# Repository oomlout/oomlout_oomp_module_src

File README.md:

# 

* ibom github: [ibom github](kicad\current_version\working\bom\ibom.html)
* ibom direct: [ibom direct](https://raw.githack.com/oomlout//main/kicad/current_version/working/bom/ibom.html)

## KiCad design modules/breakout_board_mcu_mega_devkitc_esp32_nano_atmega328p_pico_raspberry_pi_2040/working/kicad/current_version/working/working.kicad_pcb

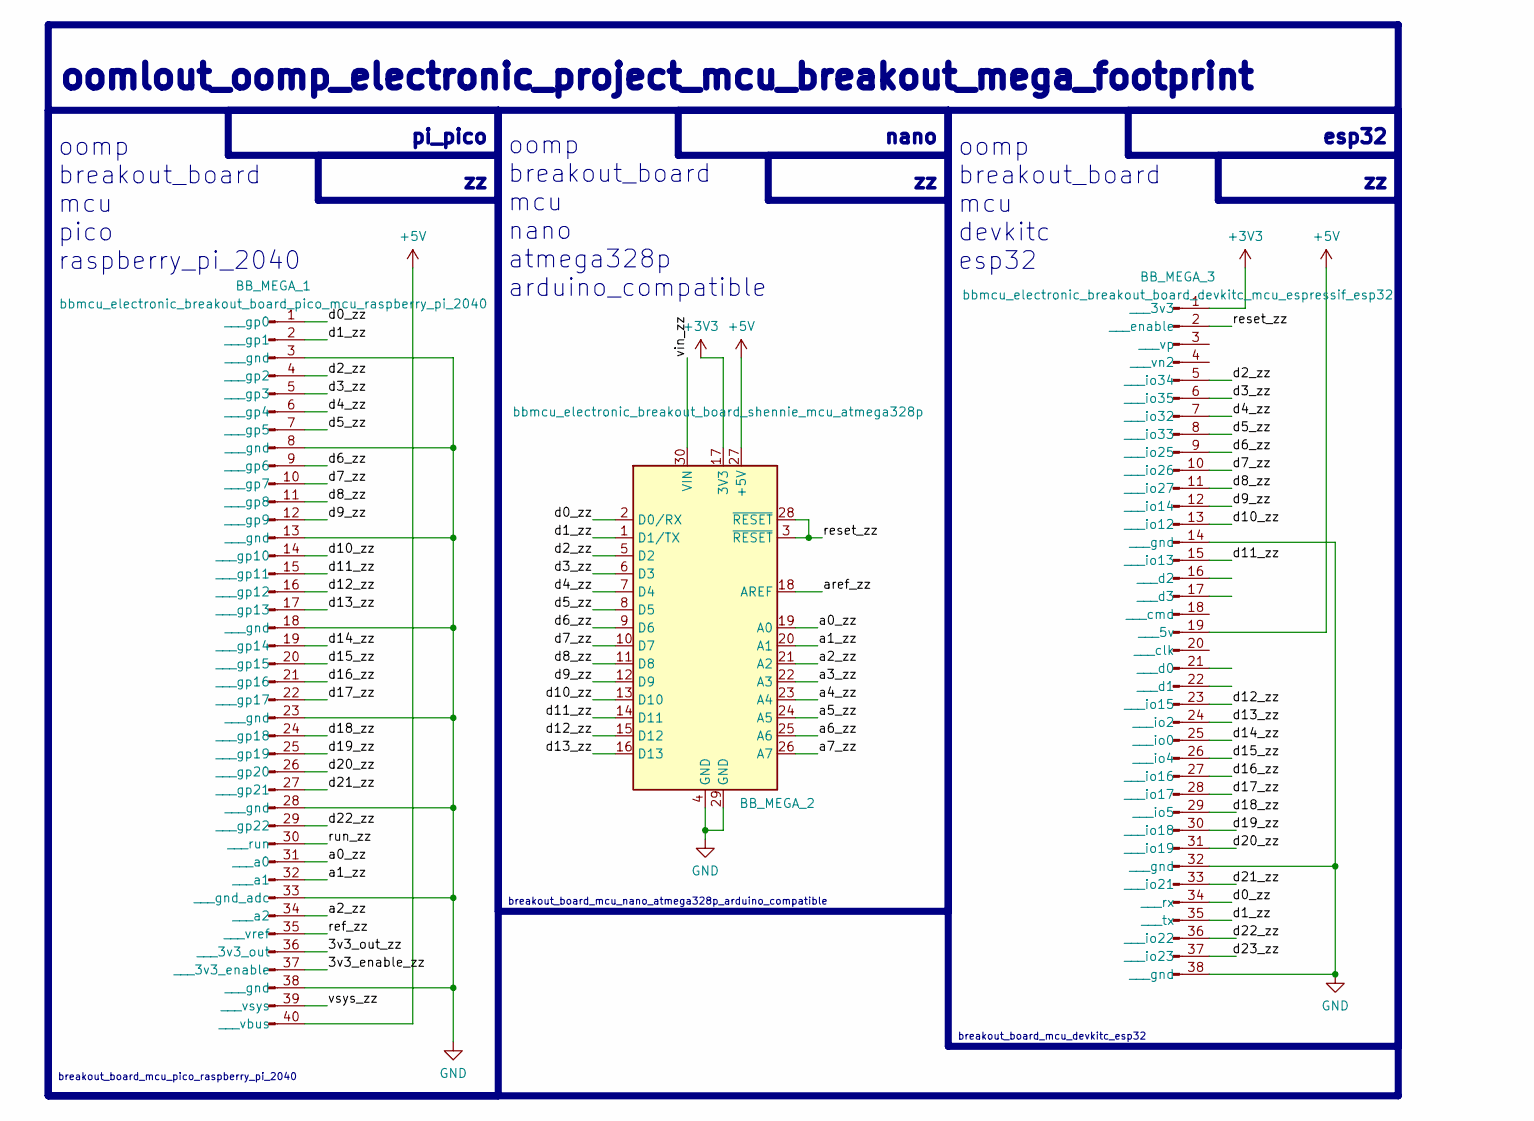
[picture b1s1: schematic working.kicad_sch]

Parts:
BB_MEGA_1: bbmcu_electronic_breakout_board_pico_mcu_raspberr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; bbmcu_electronic_breakout_board_pico_mcu_raspberry_pi_2040
BB_MEGA_2: bbmcu_electronic_breakout_board_shennie_mcu_atmeg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; bbmcu_electronic_breakout_board_shennie_mcu_atmega328p_ardu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
BB_MEGA_3: bbmcu_electronic_breakout_board_devkitc_mcu_espre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; bbmcu_electronic_breakout_board_devkitc_mcu_espressif_esp32

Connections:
+3V3: BB_MEGA_2.17 (3V3), BB_MEGA_3.1 (___3v3)
+5V: BB_MEGA_1.40 (___vbus), BB_MEGA_2.27 (+5V), BB_MEGA_3.19 (___5v)
/3v3_enable_zz: BB_MEGA_1.37 (___3v3_enable)
/3v3_out_zz: BB_MEGA_1.36 (___3v3_out)
/a0_zz: BB_MEGA_1.31 (___a0), BB_MEGA_2.19 (A0)
/a1_zz: BB_MEGA_1.32 (___a1), BB_MEGA_2.20 (A1)
/a2_zz: BB_MEGA_1.34 (___a2), BB_MEGA_2.21 (A2)
/a3_zz: BB_MEGA_2.22 (A3)
/a4_zz: BB_MEGA_2.23 (A4)
/a5_zz: BB_MEGA_2.24 (A5)
/a6_zz: BB_MEGA_2.25 (A6)
/a7_zz: BB_MEGA_2.26 (A7)
/aref_zz: BB_MEGA_2.18 (AREF)
/d0_zz: BB_MEGA_1.1 (___gp0), BB_MEGA_2.2 (D0/RX), BB_MEGA_3.34 (___rx)
/d1_zz: BB_MEGA_1.2 (___gp1), BB_MEGA_2.1 (D1/TX), BB_MEGA_3.35 (___tx)
/d2_zz: BB_MEGA_1.4 (___gp2), BB_MEGA_2.5 (D2), BB_MEGA_3.5 (___io34)
/d3_zz: BB_MEGA_1.5 (___gp3), BB_MEGA_2.6 (D3), BB_MEGA_3.6 (___io35)
/d4_zz: BB_MEGA_1.6 (___gp4), BB_MEGA_2.7 (D4), BB_MEGA_3.7 (___io32)
/d5_zz: BB_MEGA_1.7 (___gp5), BB_MEGA_2.8 (D5), BB_MEGA_3.8 (___io33)
/d6_zz: BB_MEGA_1.9 (___gp6), BB_MEGA_2.9 (D6), BB_MEGA_3.9 (___io25)
/d7_zz: BB_MEGA_1.10 (___gp7), BB_MEGA_2.10 (D7), BB_MEGA_3.10 (___io26)
/d8_zz: BB_MEGA_1.11 (___gp8), BB_MEGA_2.11 (D8), BB_MEGA_3.11 (___io27)
/d9_zz: BB_MEGA_1.12 (___gp9), BB_MEGA_2.12 (D9), BB_MEGA_3.12 (___io14)
/d10_zz: BB_MEGA_1.14 (___gp10), BB_MEGA_2.13 (D10), BB_MEGA_3.13 (___io12)
/d11_zz: BB_MEGA_1.15 (___gp11), BB_MEGA_2.14 (D11), BB_MEGA_3.15 (___io13)
/d12_zz: BB_MEGA_1.16 (___gp12), BB_MEGA_2.15 (D12), BB_MEGA_3.23 (___io15)
/d13_zz: BB_MEGA_1.17 (___gp13), BB_MEGA_2.16 (D13), BB_MEGA_3.24 (___io2)
/d14_zz: BB_MEGA_1.19 (___gp14), BB_MEGA_3.25 (___io0)
/d15_zz: BB_MEGA_1.20 (___gp15), BB_MEGA_3.26 (___io4)
/d16_zz: BB_MEGA_1.21 (___gp16), BB_MEGA_3.27 (___io16)
/d17_zz: BB_MEGA_1.22 (___gp17), BB_MEGA_3.28 (___io17)
/d18_zz: BB_MEGA_1.24 (___gp18), BB_MEGA_3.29 (___io5)
/d19_zz: BB_MEGA_1.25 (___gp19), BB_MEGA_3.30 (___io18)
/d20_zz: BB_MEGA_1.26 (___gp20), BB_MEGA_3.31 (___io19)
/d21_zz: BB_MEGA_1.27 (___gp21), BB_MEGA_3.33 (___io21)
/d22_zz: BB_MEGA_1.29 (___gp22), BB_MEGA_3.36 (___io22)
/d23_zz: BB_MEGA_3.37 (___io23)
/ref_zz: BB_MEGA_1.35 (___vref)
/reset_zz: BB_MEGA_2.3 (~RESET), BB_MEGA_2.28 (~RESET), BB_MEGA_3.2 (___enable)
/run_zz: BB_MEGA_1.30 (___run)
/vin_zz: BB_MEGA_2.30 (VIN)
/vsys_zz: BB_MEGA_1.39 (___vsys)
GND: BB_MEGA_1.3 (___gnd), BB_MEGA_1.8 (___gnd), BB_MEGA_1.13 (___gnd), BB_MEGA_1.18 (___gnd), BB_MEGA_1.23 (___gnd), BB_MEGA_1.28 (___gnd), BB_MEGA_1.33 (___gnd_adc), BB_MEGA_1.38 (___gnd), BB_MEGA_2.4 (GND), BB_MEGA_2.29 (GND), BB_MEGA_3.14 (___gnd), BB_MEGA_3.32 (___gnd), BB_MEGA_3.38 (___gnd)

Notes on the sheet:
oomlout_oomp_electronic_project_mcu_breakout_mega_footprint
oomp breakout_board mcu pico raspberry_pi_2040
nano
breakout_board_mcu_pico_raspberry_pi_2040
oomp breakout_board mcu nano atmega328p arduino_compatible
breakout_board_mcu_nano_atmega328p_arduino_compatible
pi_pico
breakout_board_mcu_devkitc_esp32
oomp breakout_board mcu devkitc esp32
esp32

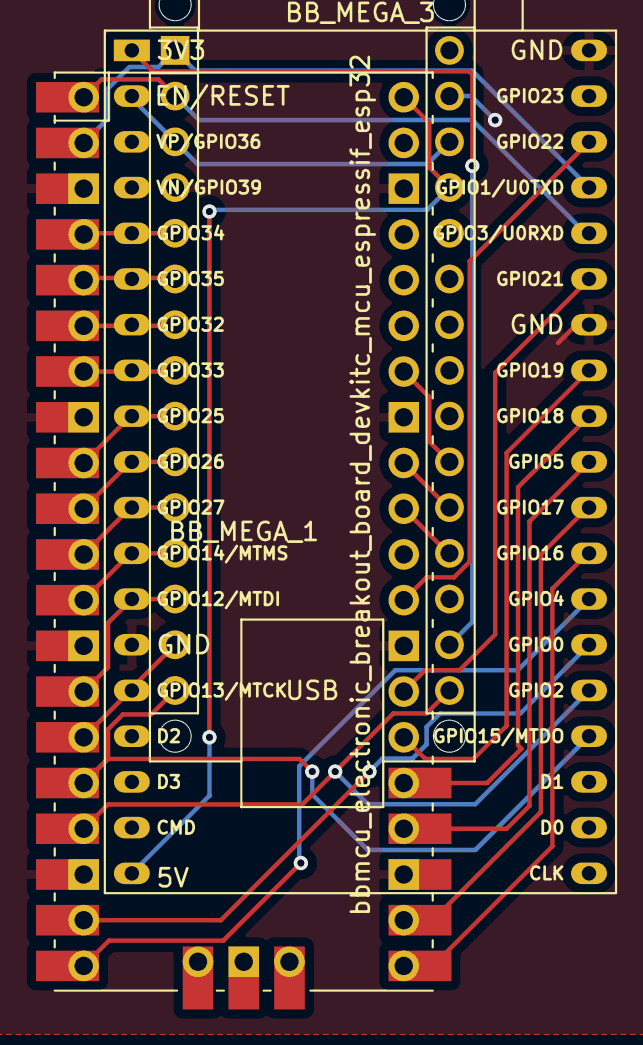
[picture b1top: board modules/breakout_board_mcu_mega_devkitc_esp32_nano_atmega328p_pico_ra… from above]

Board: 2 copper layers, 3 parts (0 on the bottom side), 30 nets.

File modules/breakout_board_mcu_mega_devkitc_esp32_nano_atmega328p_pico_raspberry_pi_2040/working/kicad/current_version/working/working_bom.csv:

"Id";"Designator";"Footprint";"Quantity";"Designation";"Supplier and ref";
1;"BB_MEGA_3";"bbmcu_electronic_breakout_board_devkitc_mcu_espressif_esp32";1;"bbmcu_electronic_breakout_board_devkitc_mcu_espressif_esp32";;;
2;"BB_MEGA_1";"bbmcu_electronic_breakout_board_pico_mcu_raspberry_pi_2040";1;"bbmcu_electronic_breakout_board_pico_mcu_raspberry_pi_2040";;;
3;"BB_MEGA_2";"bbmcu_electronic_breakout_board_shennie_mcu_atmega328p_arduino_compatible";1;"bbmcu_electronic_breakout_board_shennie_mcu_atmega328p";;;

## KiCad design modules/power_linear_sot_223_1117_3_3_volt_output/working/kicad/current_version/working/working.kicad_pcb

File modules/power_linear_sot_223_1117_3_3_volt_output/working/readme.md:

# Power Linear Sot 223 1117 3 3 Volt Output  
power_linear_sot_223_1117_3_3_volt_output  
 
## summary 
* classification: power
* type: linear
* size: sot_223
* color: 1117
* description_main: 3_3_volt_output
* description_extra: 
* id: power_linear_sot_223_1117_3_3_volt_output
* md5_6: 00fc9e
* full details link: https://github.com/oomlout/oomlout_oomp_module_src/tree/main/modules/power_linear_sot_223_1117_3_3_volt_output/working

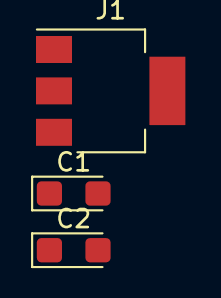
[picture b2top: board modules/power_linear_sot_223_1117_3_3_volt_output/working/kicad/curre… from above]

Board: 2 copper layers, 3 parts (0 on the bottom side), 3 nets, no tracks yet.

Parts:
C1, C2: catuf4d7_electronic_capacitor_3216_avx_a_tantalum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; catuf4d7_electronic_capacitor_3216_avx_a_tantalum_4_7_micro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
J1: pms22311173d3v_electronic_pmic_sot_223_linear_111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; pms22311173d3v_electronic_pmic_sot_223_linear_1117_3_3v

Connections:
+3V3: C2.1, J1.2 (VO)
+12V: C1.1, J1.3 (VI)
GND: C1.2, C2.2, J1.1 (GND)

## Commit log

2023-08-14 initial workings.
2023-08-18 workings
2023-08-20 gitignore update mainly and update
2023-08-24 a few module workings
2023-08-26 a few module fixes
2023-09-03 ibbc fusing
2023-09-12 works.
2023-09-12 fixed formatting to be more consistent
2023-09-12 Generated outputs
2023-09-13 module doc attempt one
2023-09-13 a few fix ups
2023-09-13 readme
2023-09-13 schematic formatting
2023-09-14 power mux added
2023-09-14 regen
2023-09-14 resolutions
2023-09-21 some works
2023-09-21 added generate
2023-09-21 commiting after auto generation
2023-09-21 add oobb connectors
